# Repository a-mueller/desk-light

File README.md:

# Desk Light

This is most likely useless for anyone else, hosting it here in case I need to make another one at some point.

## 3D Models

found in `3dPrinting`

## Board

See KiCad files.

### Schematic

### PCB

### BOM

<table>
<tr><td>R1,R2</td><td>5.1k, 0603</td><td></td></tr>
<tr><td>J1</td><td>USB4125-GF-A-0190</td><td>https://uk.farnell.com/global-connector-technology/usb4125-gf-a-0190/usb-conn-type-c-r-a-rcpt-6pos/dp/3777661</td></tr>
<tr><td>J2</td><td>JST PH 2.0 mm</td><td>alternative power, in case no USB connector used</td></tr>
<tr><td>J3</td><td>JST PH 2.0 mm</td><td>On / off switch</td></tr>
<tr><td>C1, C2</td><td>22uf, 0805</td><td></td></tr>
<tr><td>F1</td><td>Fuse 0805, 1A/1.95A</td><td>https://uk.farnell.com/yageo/smd0805b100tft/pptc-reset-fuse-smd-6vdc-0805/dp/4072028?st=smd0805b100tft</td></tr>
<tr><td>D1</td><td>Diode, MBR0540T3G 0.5A, SOD 123</td><td>https://uk.farnell.com/on-semiconductor/mbr0540t3g/diode-schottky-0-5a-40v-sod-123/dp/2101839?st=mbr0540t3g</td></tr>
<tr><td>U1</td><td>Led Driver, AL8862FF-7, 1A</td><td>https://uk.farnell.com/diodes-inc/al8862ff-7/led-dc-dc-driver-buck-u-dfn3030/dp/3946403?st=al8862ff-7</td></tr>
<tr><td>R3</td><td>0.15ohm, 0603</td><td>sets output to 1A</td></tr>
<tr><td>L1</td><td>Inductor, SRR6038-470Y</td><td>https://uk.farnell.com/bourns/srr6038-470y/power-inductor-47uh-0-95a-shielded/dp/2859255?st=srr6038-470y</td></tr>
<tr><td>D2,D3,D4</td><td>LEDs power, GW PLLRA1.EM-M8MF-XX57-1-700-R18</td><td>https://uk.farnell.com/osram-opto-semiconductors/gw-pllra1-em-m8mf-xx57-1-700/led-hb-warm-white-3000k-280lm/dp/3625393?st=gw%20pllra1.em-m8mf-xx57-1-700-r18</td></tr>

</table>

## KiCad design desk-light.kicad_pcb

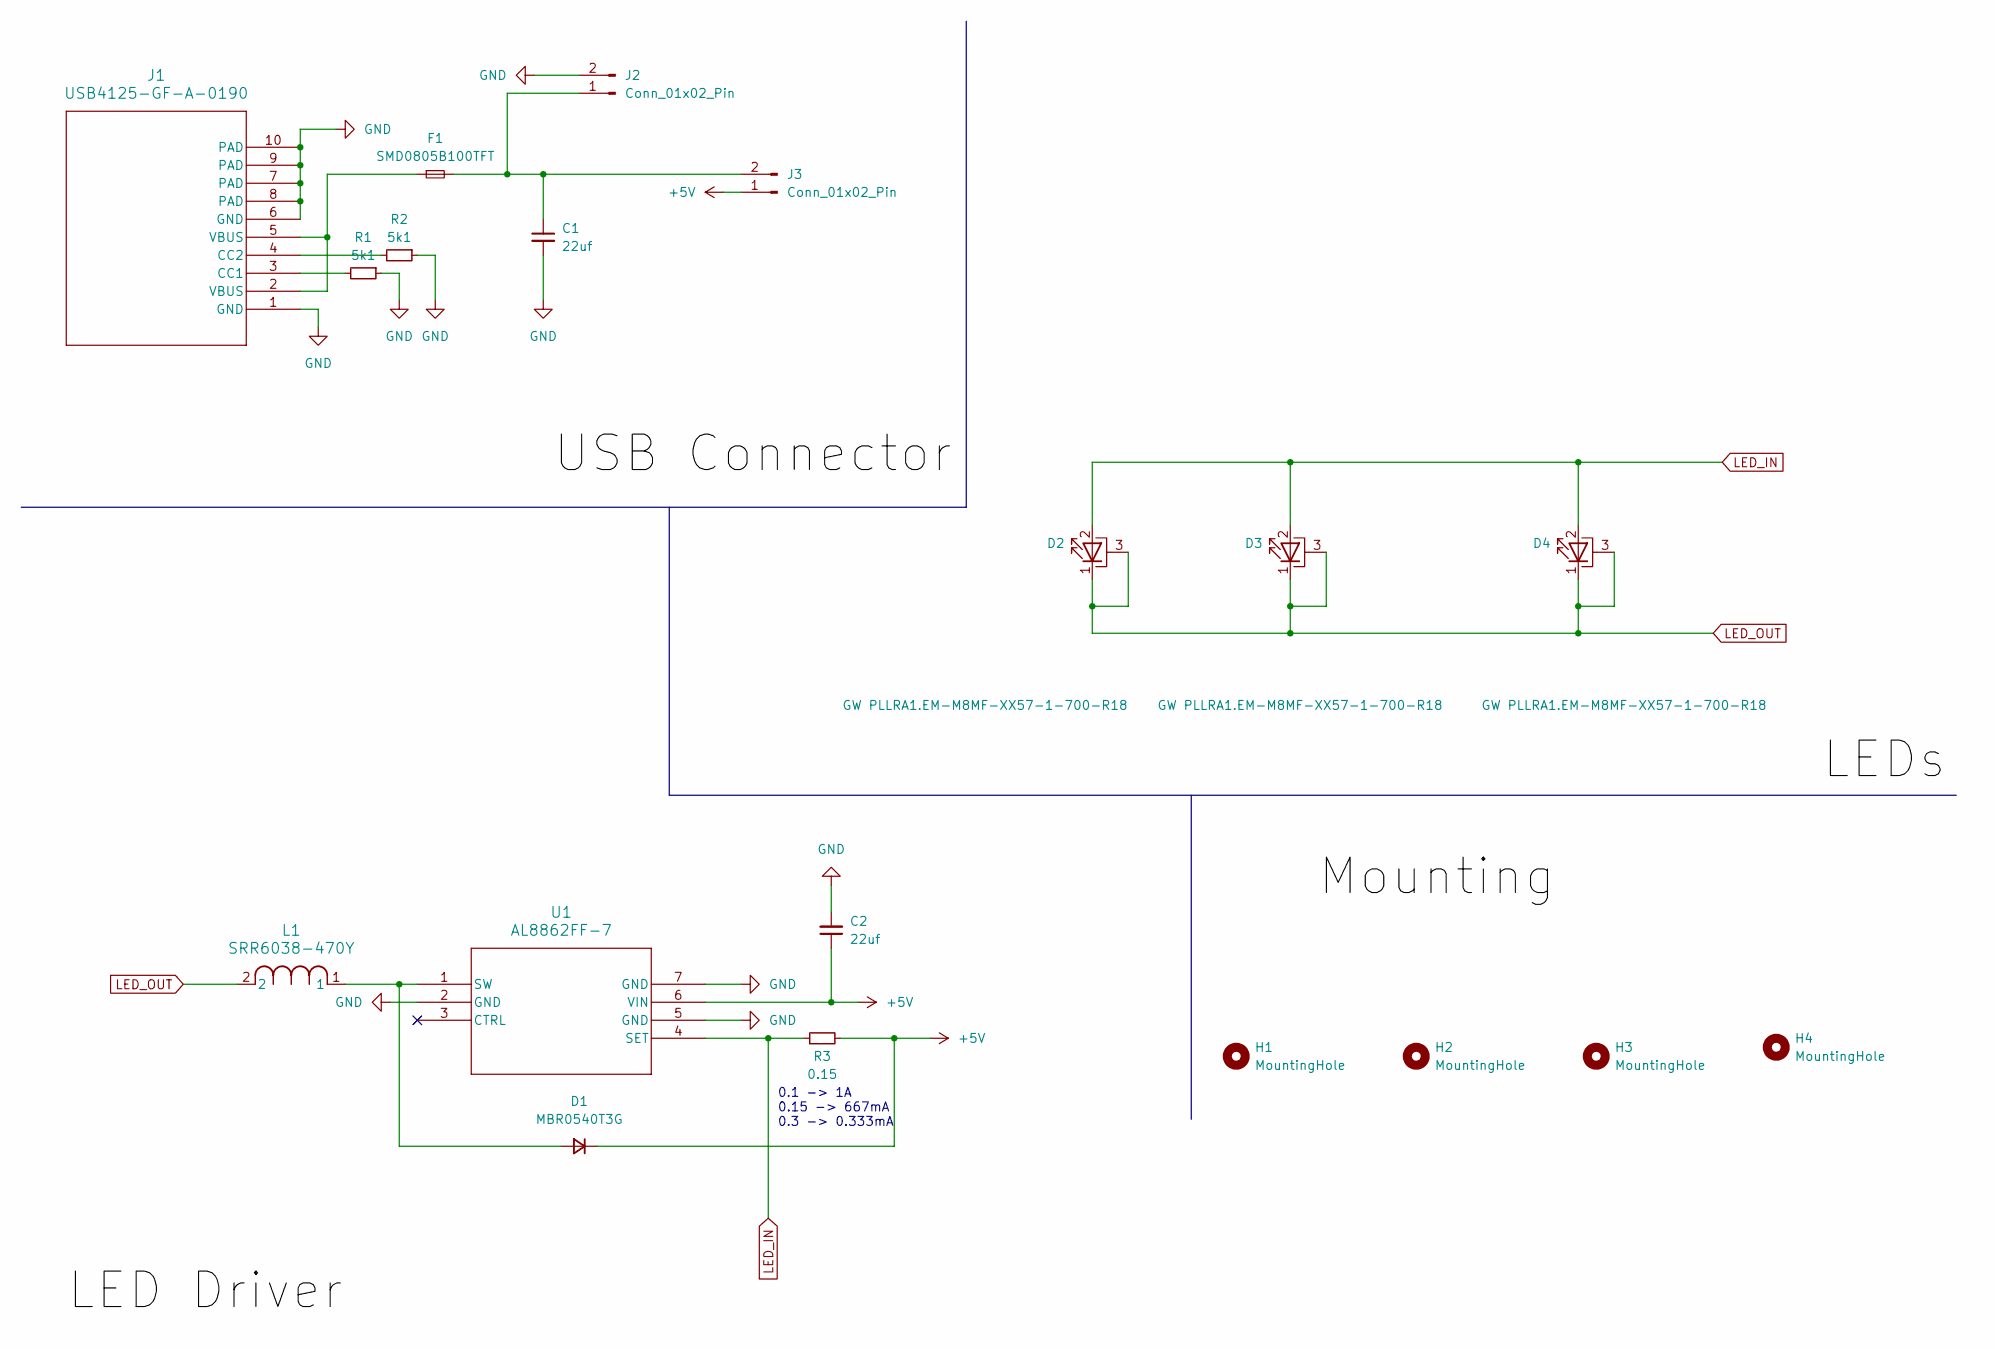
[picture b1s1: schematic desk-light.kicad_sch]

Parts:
C1, C2: 22uf; C_0805_2012Metric
D1: MBR0540T3G; SOD-123_ONS
D2, D3, D4: GW PLLRA1.EM-M8MF-XX57-1-700-R18; GWPLLRA1.EM
F1: SMD0805B100TFT; Fuse_0805_2012Metric
H1, H2, H3, H4: MountingHole; MountingHole_2.2mm_M2_DIN965_Pad
J1: USB4125-GF-A-0190; CONN6_125-GF-A-0190_GCT
J2, J3: Conn_01x02_Pin; JST_PH_B2B-PH-K_1x02_P2.00mm_Vertical
L1: SRR6038-470Y; IND_BOURNS_SRR6038
R1, R2: 5k1; ERJ6G_PAN
R3: 0.15; R_0603_1608Metric
U1: AL8862FF-7; U-DFN3030-6_DIO

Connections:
+5V: C2.1, D1.1 (K), J3.1, R3.2, U1.6 (VIN)
GND: C1.2, C2.2, J1.1 (GND), J1.6 (GND), J1.7 (PAD), J1.8 (PAD), J1.9 (PAD), J1.10 (PAD), J2.2, R1.1, R2.1, U1.2 (GND), U1.5 (GND), U1.7 (GND)
LED_IN: D2.2 (A), D3.2 (A), D4.2 (A), R3.1, U1.4 (SET)
LED_OUT: D2.1 (K), D2.3 (PAD), D3.1 (K), D3.3 (PAD), D4.1 (K), D4.3 (PAD), L1.2
unnamed: D1.2 (A), L1.1, U1.1 (SW)
unnamed: F1.1, J1.2 (VBUS), J1.5 (VBUS)
unnamed: J1.3 (CC1), R1.2
unnamed: J1.4 (CC2), R2.2
unnamed: C1.1, F1.2, J2.1, J3.2

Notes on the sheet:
0.1 -> 1A 0.15 -> 667mA 0.3 -> 0.333mA

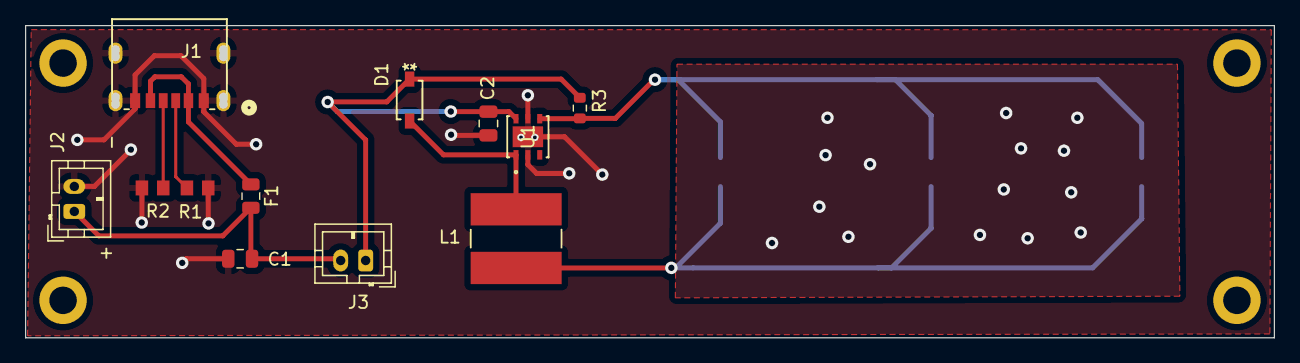
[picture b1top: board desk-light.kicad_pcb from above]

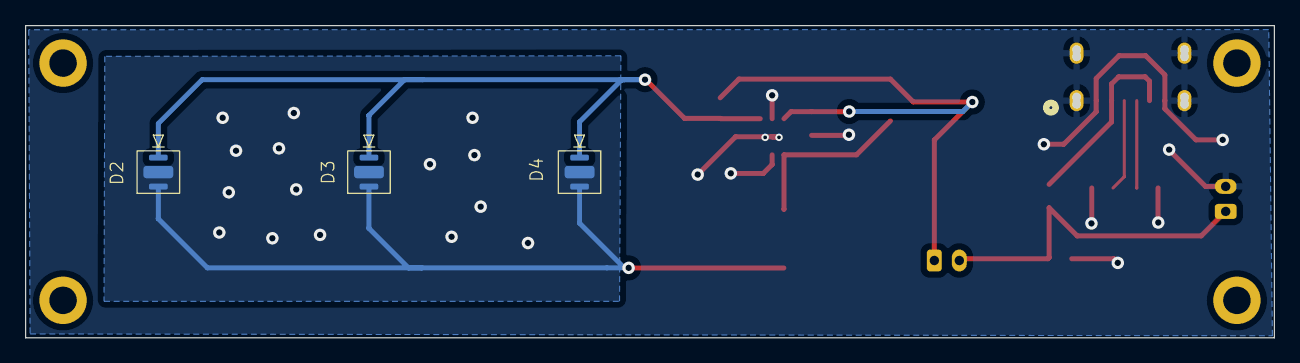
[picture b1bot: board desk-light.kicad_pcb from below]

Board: 2 copper layers, 99.5 x 24.5 mm, 19 parts (3 on the bottom side), 9 nets.
